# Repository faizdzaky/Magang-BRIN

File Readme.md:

# Dokumentasi & Repositori Pembelajaran Pemrograman Embedded Systems

Folder ini berisi latihan, kode program hasil pembelajaran, dan rangkaian dari KiCad yang dilakuakn selama magang di Brin.

## 📁 Struktur dan Isi Folder

Berikut adalah penjelasan fungsi dan cakupan materi dari masing-masing folder di dalam repositori ini:

### 1. `01-Kodingan/`
Folder ini berisi latihan dan kode program hasil pembelajaran mengenai pemrosesan sinyal digital, komunikasi mikrokarakter/mikroprosesor, serta pengontrolan I/O.
* **Materi:** Pembelajaran dari kodingan tentang ADC, Blok dan nonblok, serialport, onewire, LED, dan digital input output.

### 2. `02-PCB/`
Folder ini berisi latihan pembuat PCB di kiCad dari rangkaian simpel sampai ke rangkaian yg lebih advanced.
* **Materi:** beberapa rangkaian PCB yang telah dibuat seperti simpel, advanced, platform arduino pro mini, dan kontrol tomografi.

---

## 🛠️ Prasyarat & Perangkat yang Digunakan buat kodingan
* **Hardware:** Mikrokontroler (Arduino), LED, Resistor, Potensiometer/Sensor Analog, Sensor OneWire (DS18B20).
* **Software/IDE:** Arduino IDE / VS Code + PlatformIO.

## 🛠️ Prasyarat & Perangkat yang Digunakan buat kodingan
* **Software/IDE:** KiCad.

## 🚀 Cara Menggunakan
1. Clone repositori ini ke komputer lokal kamu:
   ```bash
   git clone https://github.com/faizdzaky/Magang-BRIN.git <YOUR_PROJECT_DIR>
    cd <YOUR_PROJECT_DIR>

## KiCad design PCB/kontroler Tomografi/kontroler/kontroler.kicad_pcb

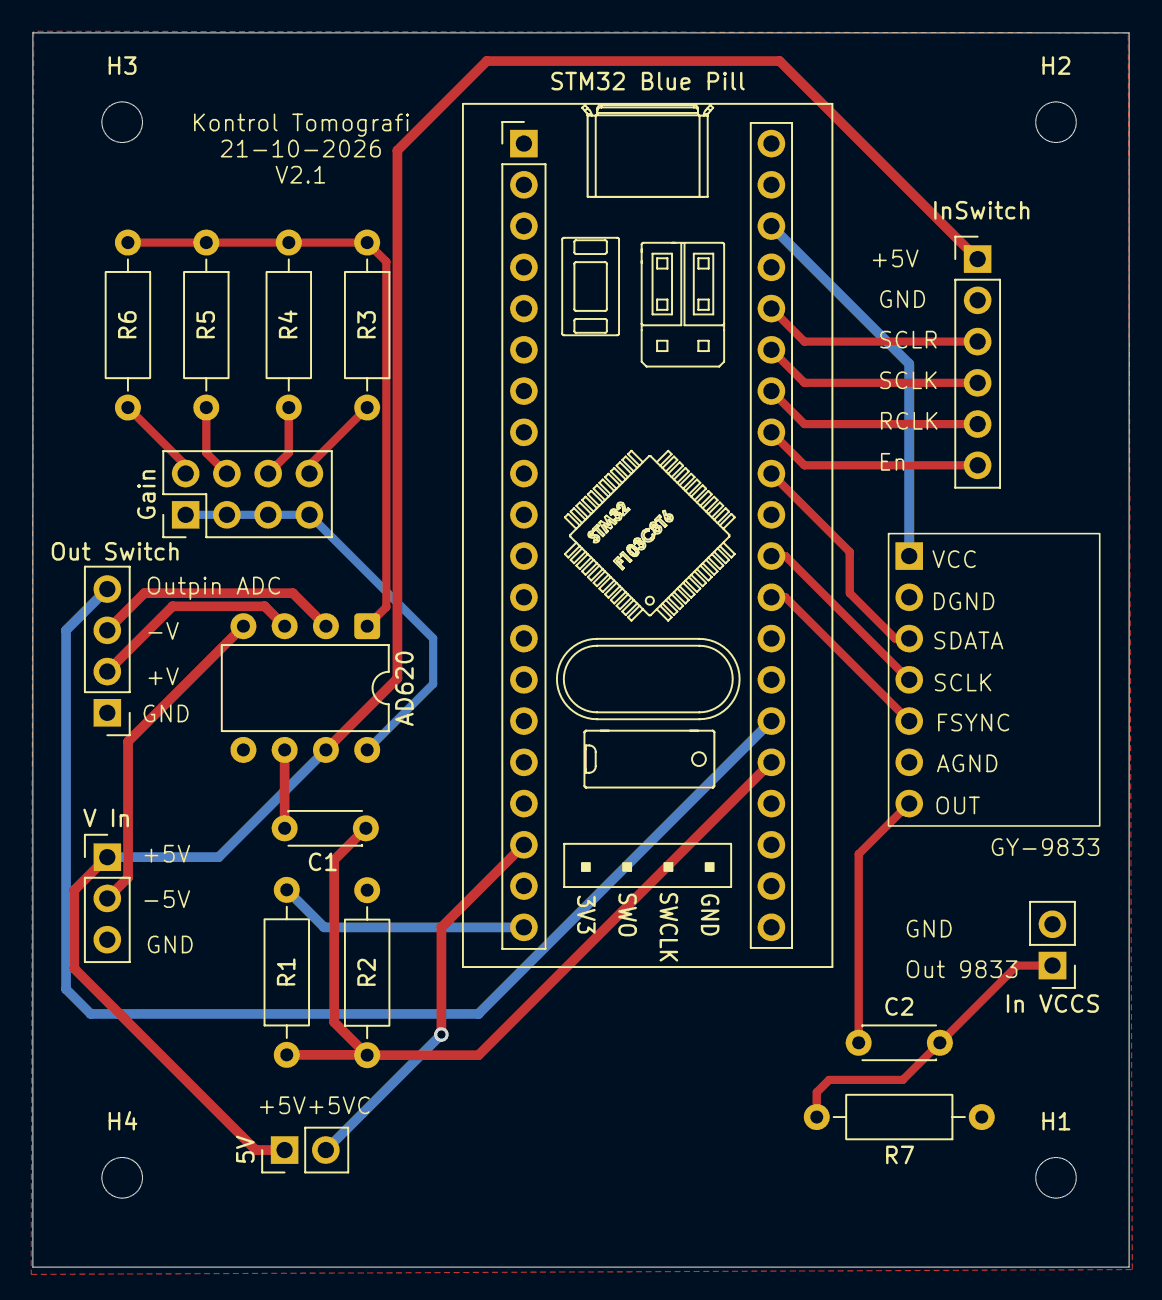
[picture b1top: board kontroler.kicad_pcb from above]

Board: 4 copper layers, 67.5 x 76.0 mm, 22 parts (0 on the bottom side), 25 nets.

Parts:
5V: V 5V; PinHeader_1x02_P2.54mm_Vertical
AD620: AD620; DIP-8_W7.62mm
C1: 100n F; C_Disc_D4.3mm_W1.9mm_P5.00mm
C2: C; C_Disc_D4.3mm_W1.9mm_P5.00mm
Gain: Conn_02x04_Odd_Even; PinHeader_2x04_P2.54mm_Vertical
H1, H2, H3, H4: MountingHole; MountingHole_2.5mm
In VCCS: In_VCCS; PinHeader_1x02_P2.54mm_Vertical
InSwitch: In_Switch; PinHeader_1x06_P2.54mm_Vertical
Out Switch: Out_Switch; PinHeader_1x04_P2.54mm_Vertical
R1, R2: 10k; R_Axial_DIN0207_L6.3mm_D2.5mm_P10.16mm_Horizontal
R3: 499; R_Axial_DIN0207_L6.3mm_D2.5mm_P10.16mm_Horizontal
R4: 5.94k; R_Axial_DIN0207_L6.3mm_D2.5mm_P10.16mm_Horizontal
R5, R6: 49.4k; R_Axial_DIN0207_L6.3mm_D2.5mm_P10.16mm_Horizontal
R7: R; R_Axial_DIN0207_L6.3mm_D2.5mm_P10.16mm_Horizontal
STM32 Blue Pill: YAAJ_BluePill; YAAJ_BluePill_1
U3: AD9833 Modul
V In: V_In; PinHeader_1x03_P2.54mm_Vertical

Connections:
+3.3V: R1.2, STM32 Blue Pill.20 (3V3), STM32 Blue Pill.38 (3V3), U3.1 (VCC)
+5V: 5V.2, STM32 Blue Pill.18 (5V)
+5VA: 5V.1, AD620.7 (Vs+), InSwitch.1, V In.1
-5V: AD620.4 (Vs-), V In.2
/+V: AD620.3 (+), Out Switch.2
/-V: AD620.2 (-), Out Switch.3
/En: InSwitch.6, STM32 Blue Pill.33 (PB0)
/FSYNC: STM32 Blue Pill.29 (PA4), U3.5 (FSYNC)
/Out 9833: C2.1, U3.7 (OUT)
/Out ADC: C1.2, R1.1, R2.1, STM32 Blue Pill.25 (PA0)
/Out HPF: C2.2, In VCCS.1, R7.2
/Out pin ADC: Out Switch.4, STM32 Blue Pill.26 (PA1)
/RCLK: InSwitch.5, STM32 Blue Pill.34 (PB1)
/SCLK1: STM32 Blue Pill.30 (PA5), U3.4 (SCLK)
/SCLK2: InSwitch.4, STM32 Blue Pill.35 (PB10)
/SCLR: InSwitch.3, STM32 Blue Pill.36 (PB11)
/SDATA: STM32 Blue Pill.32 (PA7), U3.3 (SDATA)
GND: AD620.5 (Ref), In VCCS.2, InSwitch.2, Out Switch.1, R2.2, R7.1, STM32 Blue Pill.19 (GND), STM32 Blue Pill.39 (GND), STM32 Blue Pill.40 (GND), U3.2 (DGND), U3.6 (AGND), V In.3
unnamed: AD620.6, C1.1
unnamed: AD620.8 (Rg), Gain.1, Gain.3, Gain.5, Gain.7
unnamed: Gain.2, R6.2
unnamed: Gain.4, R5.2
unnamed: Gain.6, R4.2
unnamed: Gain.8, R3.2
unnamed: AD620.1 (Rg), R3.1, R4.1, R5.1, R6.1

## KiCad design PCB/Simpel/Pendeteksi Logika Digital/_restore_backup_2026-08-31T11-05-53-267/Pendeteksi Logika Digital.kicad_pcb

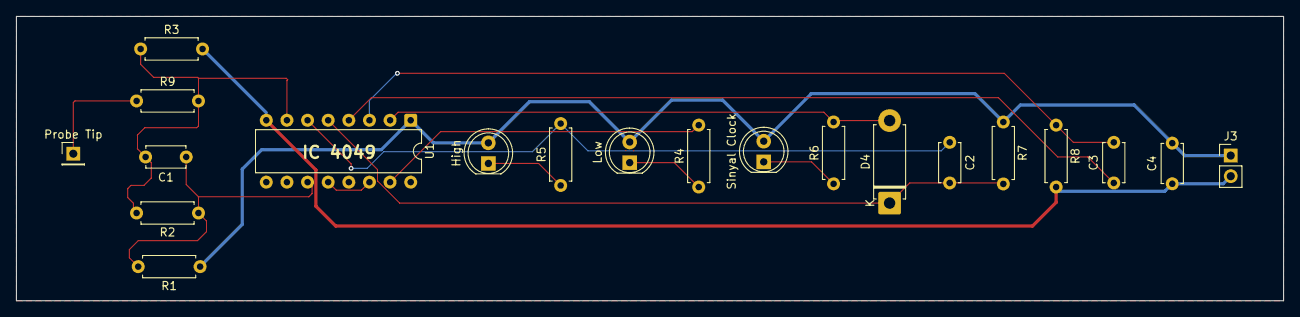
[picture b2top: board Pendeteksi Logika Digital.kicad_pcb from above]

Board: 4 copper layers, 156.0 x 35.0 mm, 20 parts (0 on the bottom side), 15 nets.

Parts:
C1, C2: 100p; C_Disc_D4.7mm_W2.5mm_P5.00mm
C3: 100n; C_Disc_D4.7mm_W2.5mm_P5.00mm
C4: 10n; C_Disc_D4.7mm_W2.5mm_P5.00mm
D4: D; D_5W_P10.16mm_Horizontal
High: LED; LED_D5.0mm
J3: Conn_01x02_Pin; PinHeader_1x02_P2.54mm_Vertical
Low: LED; LED_D5.0mm
Probe Tip: Conn_01x01_Pin; PinHeader_1x01_P2.54mm_Vertical
R1, R7: 2M2; R_Axial_DIN0207_L6.3mm_D2.5mm_P7.62mm_Horizontal
R2: 680k; R_Axial_DIN0207_L6.3mm_D2.5mm_P7.62mm_Horizontal
R3: 560k; R_Axial_DIN0207_L6.3mm_D2.5mm_P7.62mm_Horizontal
R4, R5, R6: 820R; R_Axial_DIN0207_L6.3mm_D2.5mm_P7.62mm_Horizontal
R8: 220k; R_Axial_DIN0207_L6.3mm_D2.5mm_P7.62mm_Horizontal
R9: 1k; R_Axial_DIN0207_L6.3mm_D2.5mm_P7.62mm_Horizontal
Sinyal Clock: LED; LED_D5.0mm
U1: 4049; DIP-16_W7.62mm

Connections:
GND: C4.1, J3.2, R3.2, R8.2, U1.8 (VSS)
unnamed: C1.1, R1.2, R2.1, U1.11
unnamed: C1.2, R2.2, R3.1, R9.2, U1.7
unnamed: C2.1, R5.2, U1.6
unnamed: C3.1, U1.4
unnamed: C3.2, R8.1, U1.3
unnamed: Low.1 (K), R4.1
unnamed: High.1 (K), R5.1
unnamed: R6.1, Sinyal Clock.1 (K)
unnamed: D4.2 (A), R6.2, U1.2
unnamed: C2.2, D4.1 (K), R7.2, U1.5
unnamed: Probe Tip.1 (Pin_1_1), R9.1
unnamed: R4.2, U1.15
unnamed: U1.12, U1.14
VCC: C4.2, High.2 (A), J3.1, Low.2 (A), R1.1, R7.1, Sinyal Clock.2 (A), U1.1 (VCC)

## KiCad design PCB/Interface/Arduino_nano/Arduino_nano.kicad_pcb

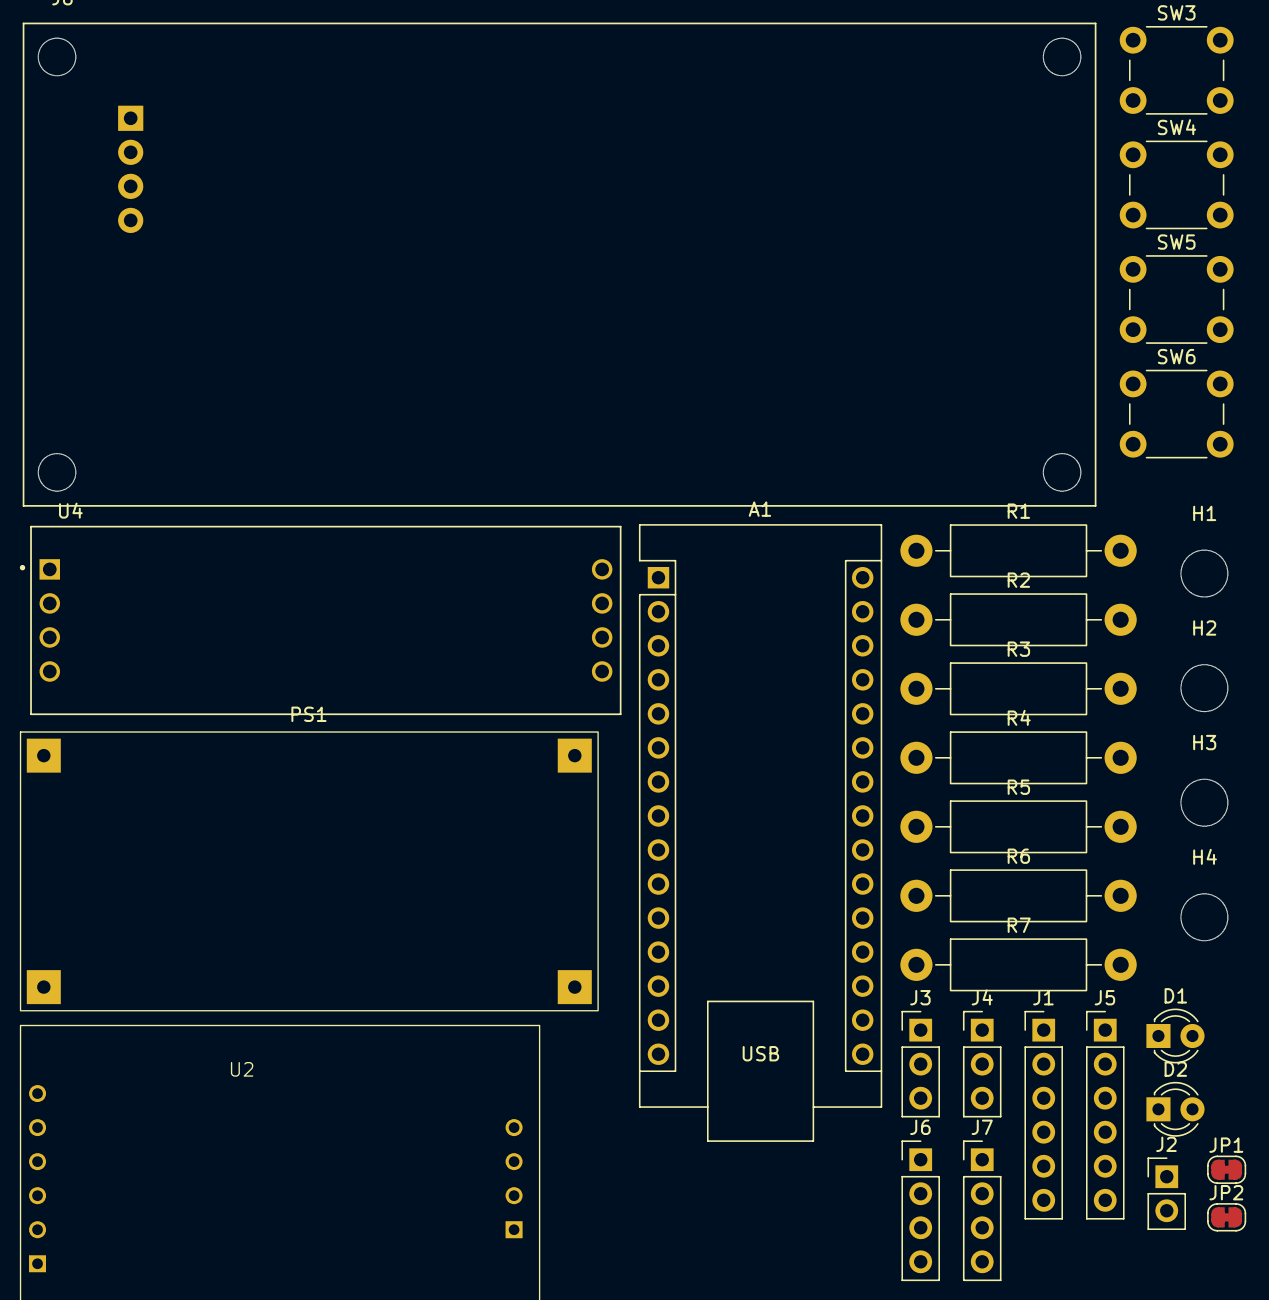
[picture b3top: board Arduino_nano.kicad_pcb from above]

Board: 4 copper layers, 31 parts (0 on the bottom side), 35 nets, no tracks yet.

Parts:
A1: Arduino_Nano_v3.x; Arduino_Nano
D1, D2: LED; LED_D3.0mm
H1, H2, H3, H4: MountingHole; MountingHole_3.5mm
J1: SPI; PinHeader_1x06_P2.54mm_Vertical
J2: Pin Out RS485; PinHeader_1x02_P2.54mm_Vertical
J3, J4: Conn_01x03; PinHeader_1x03_P2.54mm_Vertical
J5: Analog sisa; PinHeader_1x06_P2.54mm_Vertical
J6: Pin I2C; PinHeader_1x04_P2.54mm_Vertical
J7: Serial Port; PinHeader_1x04_P2.54mm_Vertical
J8: LCD; MODULE_LCD-16X2
JP1, JP2: SolderJumper_2_Open; SolderJumper-2_P1.3mm_Bridged_RoundedPad1.0x1.5mm
PS1: LM2596_Module; LM2596-DC-DC
R1, R2: 330; R_Axial_DIN0411_L9.9mm_D3.6mm_P15.24mm_Horizontal
R3, R4, R5, R6: 4.7k; R_Axial_DIN0411_L9.9mm_D3.6mm_P15.24mm_Horizontal
R7: 10k; R_Axial_DIN0411_L9.9mm_D3.6mm_P15.24mm_Horizontal
SW3, SW4, SW5, SW6: SW_Push; SW_PUSH_6mm
U2: DS3231M; MODULE_DS3231
U4: MAX485_MODULE_5V_LOGIC_TLL_TO_RS-485_CONVERTER; MODULE_MAX485_MODULE_5V_LOGIC_TLL_TO_RS-485_CONVERTER

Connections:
+5V: A1.27 (+5V), J1.6, J3.2, J6.1, J7.4, J8.1, PS1.1 (IN+), R3.1, R4.1, R5.1, U2.2 (VCC), U4.4 (VCC)
/3V3: A1.17 (3V3), J4.2
/A0: A1.19 (A0), J6.3, J8.3, R4.2
/A1: A1.20 (A1), J6.4, J8.4, R3.2
/A2: A1.21 (A2), J5.6
/A3: A1.22 (A3), J5.5
/A4: A1.23 (A4), J5.4
/A5: A1.24 (A5), J5.3
/A6: A1.25 (A6), J5.2
/A7: A1.26 (A7), J5.1
/D0: A1.2 (D0/RX), J7.2
/D1: A1.1 (D1/TX), J7.1
/D2: A1.5 (D2), J4.1
/D3: A1.6 (D3), U4.8 (DI)
/D4: A1.7 (D4), U4.5 (RO)
/D5: A1.8 (D5), R7.1, U4.6 (RE), U4.7 (DE)
/D6: A1.9 (D6), SW5.1
/D7: A1.10 (D7), SW6.1
/D8: A1.11 (D8), R1.2
/D9: A1.12 (D9), R2.2
/D10: A1.13 (D10), J1.4
/D11: A1.14 (D11), J1.3
/D12: A1.15 (D12), J1.2
/D13: A1.16 (D13), J1.1
/RESET1: A1.28 (~RESET), SW3.1
/RESET2: A1.3 (~RESET), SW4.1
/Vin: A1.30 (VIN), J4.3
GND: A1.4 (GND), A1.29 (GND), D1.1 (K), D2.1 (K), J1.5, J3.1, J6.2, J7.3, J8.2, PS1.2 (IN-), PS1.3 (OUT-), R6.2, R7.2, SW3.2, SW4.2, SW5.2, SW6.2, U2.5 (GND), U2.6 (GND), U4.1 (GND)
unnamed: D1.2 (A), JP1.1 (A)
unnamed: D2.2 (A), JP2.1 (A)
unnamed: J2.1, R5.2, U4.2 (A)
unnamed: J2.2, R6.1, U4.3 (B)
unnamed: J3.3, PS1.4 (OUT+)
unnamed: JP1.2 (B), R1.1
unnamed: JP2.2 (B), R2.1

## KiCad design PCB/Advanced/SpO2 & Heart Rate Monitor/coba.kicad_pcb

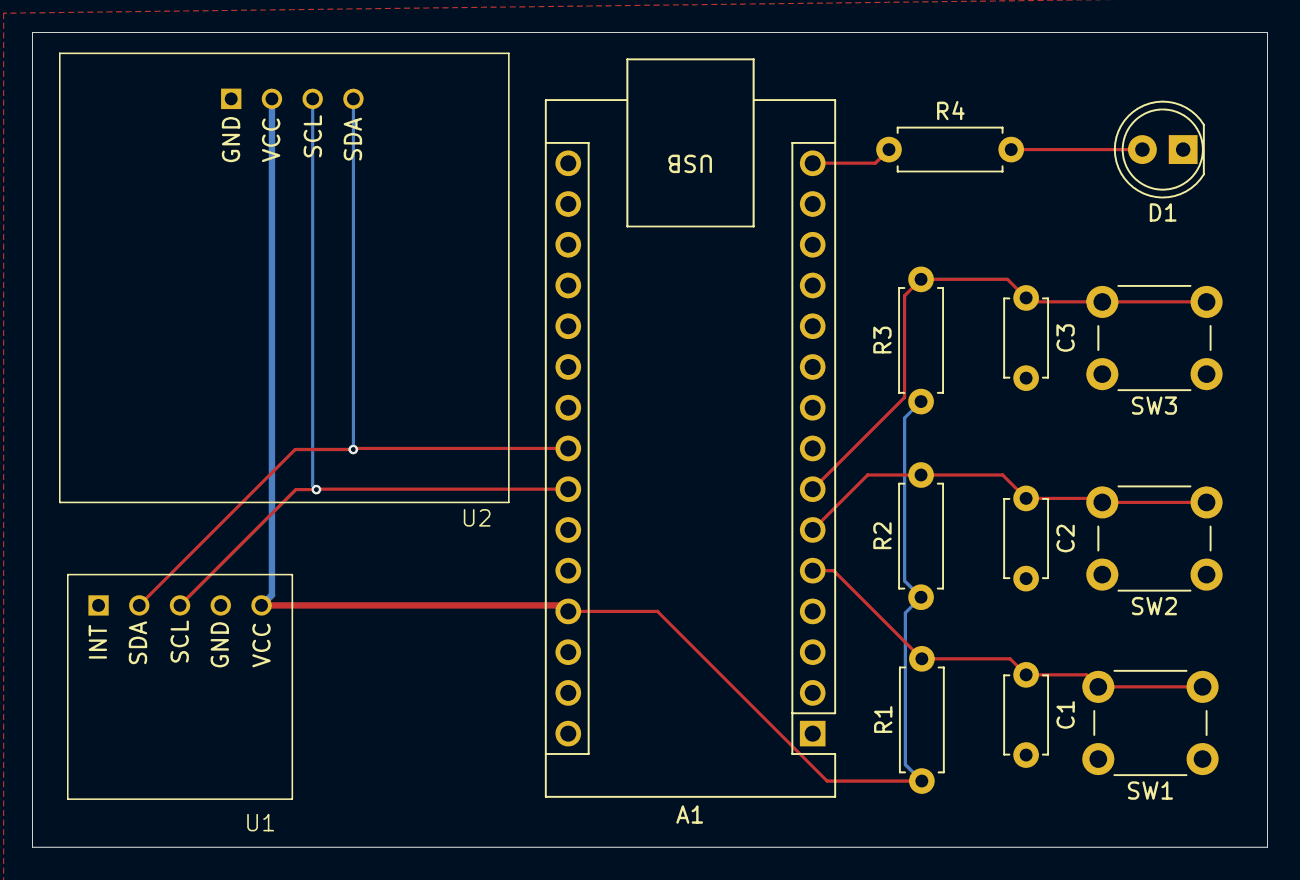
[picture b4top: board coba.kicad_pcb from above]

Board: 4 copper layers, 77.0 x 50.8 mm, 14 parts (0 on the bottom side), 9 nets.

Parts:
A1: Arduino_Nano_v3.x; Arduino_Nano
C1, C2, C3: 100n; C_Disc_D4.7mm_W2.5mm_P5.00mm
D1: LED; LED_D5.0mm
R1, R2, R3, R4: 1K; R_Axial_DIN0207_L6.3mm_D2.5mm_P7.62mm_Horizontal
SW1, SW2, SW3: SW_Push; SW_PUSH_6mm
U1: MAX30102; MAX30102_Module
U2: SSD1306

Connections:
+5V: A1.27 (+5V), R1.1, R2.1, R3.1, U1.5 (VCC), U2.2 (VCC)
GND: A1.4 (GND), A1.29 (GND), C1.2, C2.2, C3.2, D1.1 (K), SW1.1, SW2.1, SW3.1, U1.4 (GND), U2.1 (GND)
unnamed: A1.23 (A4), U1.2 (SDA), U2.4 (SDA)
unnamed: A1.24 (A5), U1.3 (SCL), U2.3 (SCL)
unnamed: A1.5 (D2), C1.1, R1.2, SW1.2
unnamed: A1.6 (D3), C2.1, R2.2, SW2.2
unnamed: A1.7 (D4), C3.1, R3.2, SW3.2
unnamed: A1.15 (D12), R4.1
unnamed: D1.2 (A), R4.2

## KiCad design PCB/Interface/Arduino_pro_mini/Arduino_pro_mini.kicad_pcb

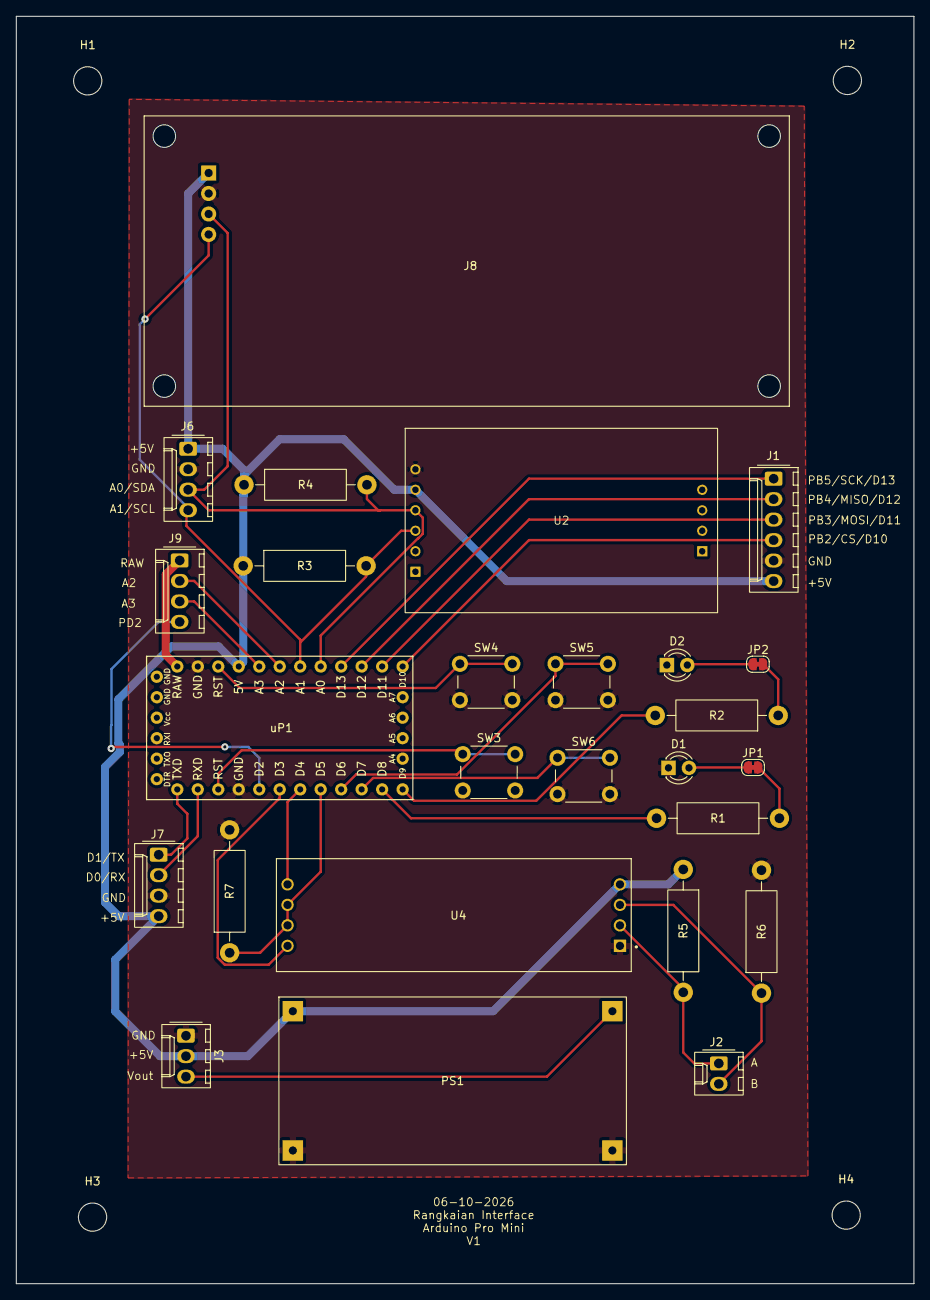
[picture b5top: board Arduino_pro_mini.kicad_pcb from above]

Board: 4 copper layers, 111.3 x 157.2 mm, 30 parts (0 on the bottom side), 30 nets.

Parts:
D1, D2: LED; LED_D3.0mm
H1, H2, H3, H4: MountingHole; MountingHole_3.5mm
J1: SPI; Molex_KK-254_AE-6410-06A_1x06_P2.54mm_Vertical
J2: Pin Out RS485; Molex_KK-254_AE-6410-02A_1x02_P2.54mm_Vertical
J3: Conn_01x03; Molex_KK-254_AE-6410-03A_1x03_P2.54mm_Vertical
J6: Pin I2C; Molex_KK-254_AE-6410-04A_1x04_P2.54mm_Vertical
J7: Serial Port; Molex_KK-254_AE-6410-04A_1x04_P2.54mm_Vertical
J8: LCD; MODULE_LCD-16X2
J9: yg gk kepake; Molex_KK-254_AE-6410-04A_1x04_P2.54mm_Vertical
JP1, JP2: SolderJumper_2_Open; SolderJumper-2_P1.3mm_Bridged_RoundedPad1.0x1.5mm
PS1: LM2596_Module; LM2596-DC-DC
R1, R2: 330; R_Axial_DIN0411_L9.9mm_D3.6mm_P15.24mm_Horizontal
R3, R4, R5, R6: 4.7k; R_Axial_DIN0411_L9.9mm_D3.6mm_P15.24mm_Horizontal
R7: 10k; R_Axial_DIN0411_L9.9mm_D3.6mm_P15.24mm_Horizontal
SW3, SW4, SW5, SW6: SW_Push; SW_PUSH_6mm
U2: DS3231M; MODULE_DS3231
U4: MAX485_MODULE_5V_LOGIC_TLL_TO_RS-485_CONVERTER; MODULE_MAX485_MODULE_5V_LOGIC_TLL_TO_RS-485_CONVERTER
uP1: ProMini2; Pro_Mini

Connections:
+5V: J1.6, J3.2, J6.1, J7.4, J8.1, PS1.1 (IN+), R3.1, R4.1, R5.1, U2.5 (GND), U4.4 (VCC), uP1.22 (Vcc/5v)
/A0: J6.3, J8.3, R4.2, U2.4 (~RST), uP1.26 (PC0/A0)
/A1: J6.4, J8.4, R3.2, U2.3 (~INT/SQW), uP1.25 (PC1/A1)
/A2: J9.2, uP1.24 (PC2/A2)
/A3: J9.3, uP1.23 (PC3/A3)
/D0: J7.2, uP1.8 (RX_D0)
/D1: J7.1, uP1.7 (TX0_D1)
/PB0: R1.2, uP1.17 (PB0)
/PB1: R2.2, uP1.18 (PB1)
/PB2: J1.4, uP1.30 (PB2)
/PB3: J1.3, uP1.29 (PB3)
/PB4: J1.2, uP1.28 (PB4)
/PB5: J1.1, uP1.27 (PB5)
/PD2: J9.4, uP1.11 (PD2)
/PD3: U4.8 (DI), uP1.12 (PD3)
/PD4: U4.5 (RO), uP1.13 (PD4)
/PD5: R7.1, U4.6 (RE), U4.7 (DE), uP1.14 (PD5)
/PD6: SW5.1, uP1.15 (PD6)
/PD7: SW6.1, uP1.16 (PD7)
/RAW: J9.1, uP1.19 (RAW)
/RESET1: SW3.1, uP1.9 (RESET)
/RESET2: SW4.1, uP1.21 (RESET)
GND: D1.1 (K), D2.1 (K), J1.5, J3.1, J6.2, J7.3, J8.2, PS1.2 (IN-), PS1.3 (OUT-), R6.2, R7.2, SW3.2, SW4.2, SW5.2, SW6.2, U2.6 (GND), U4.1 (GND), uP1.10 (GND), uP1.20 (GND)
unnamed: D1.2 (A), JP1.1 (A)
unnamed: D2.2 (A), JP2.1 (A)
unnamed: J2.1, R5.2, U4.2 (A)
unnamed: J2.2, R6.1, U4.3 (B)
unnamed: J3.3, PS1.4 (OUT+)
unnamed: JP1.2 (B), R1.1
unnamed: JP2.2 (B), R2.1
